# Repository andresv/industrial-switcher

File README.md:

## industrial-switcher

This board is meant for switching various 24V loads, like coils and relays.

## Requirements

[PlatformIO](http://platformio.org) is used for building.

```
pip install -U pip setuptools
pip install -U platformio
platformio platforms install timsp430
```

## Build and upload
```
platformio run
platformio run --target upload
```

## License

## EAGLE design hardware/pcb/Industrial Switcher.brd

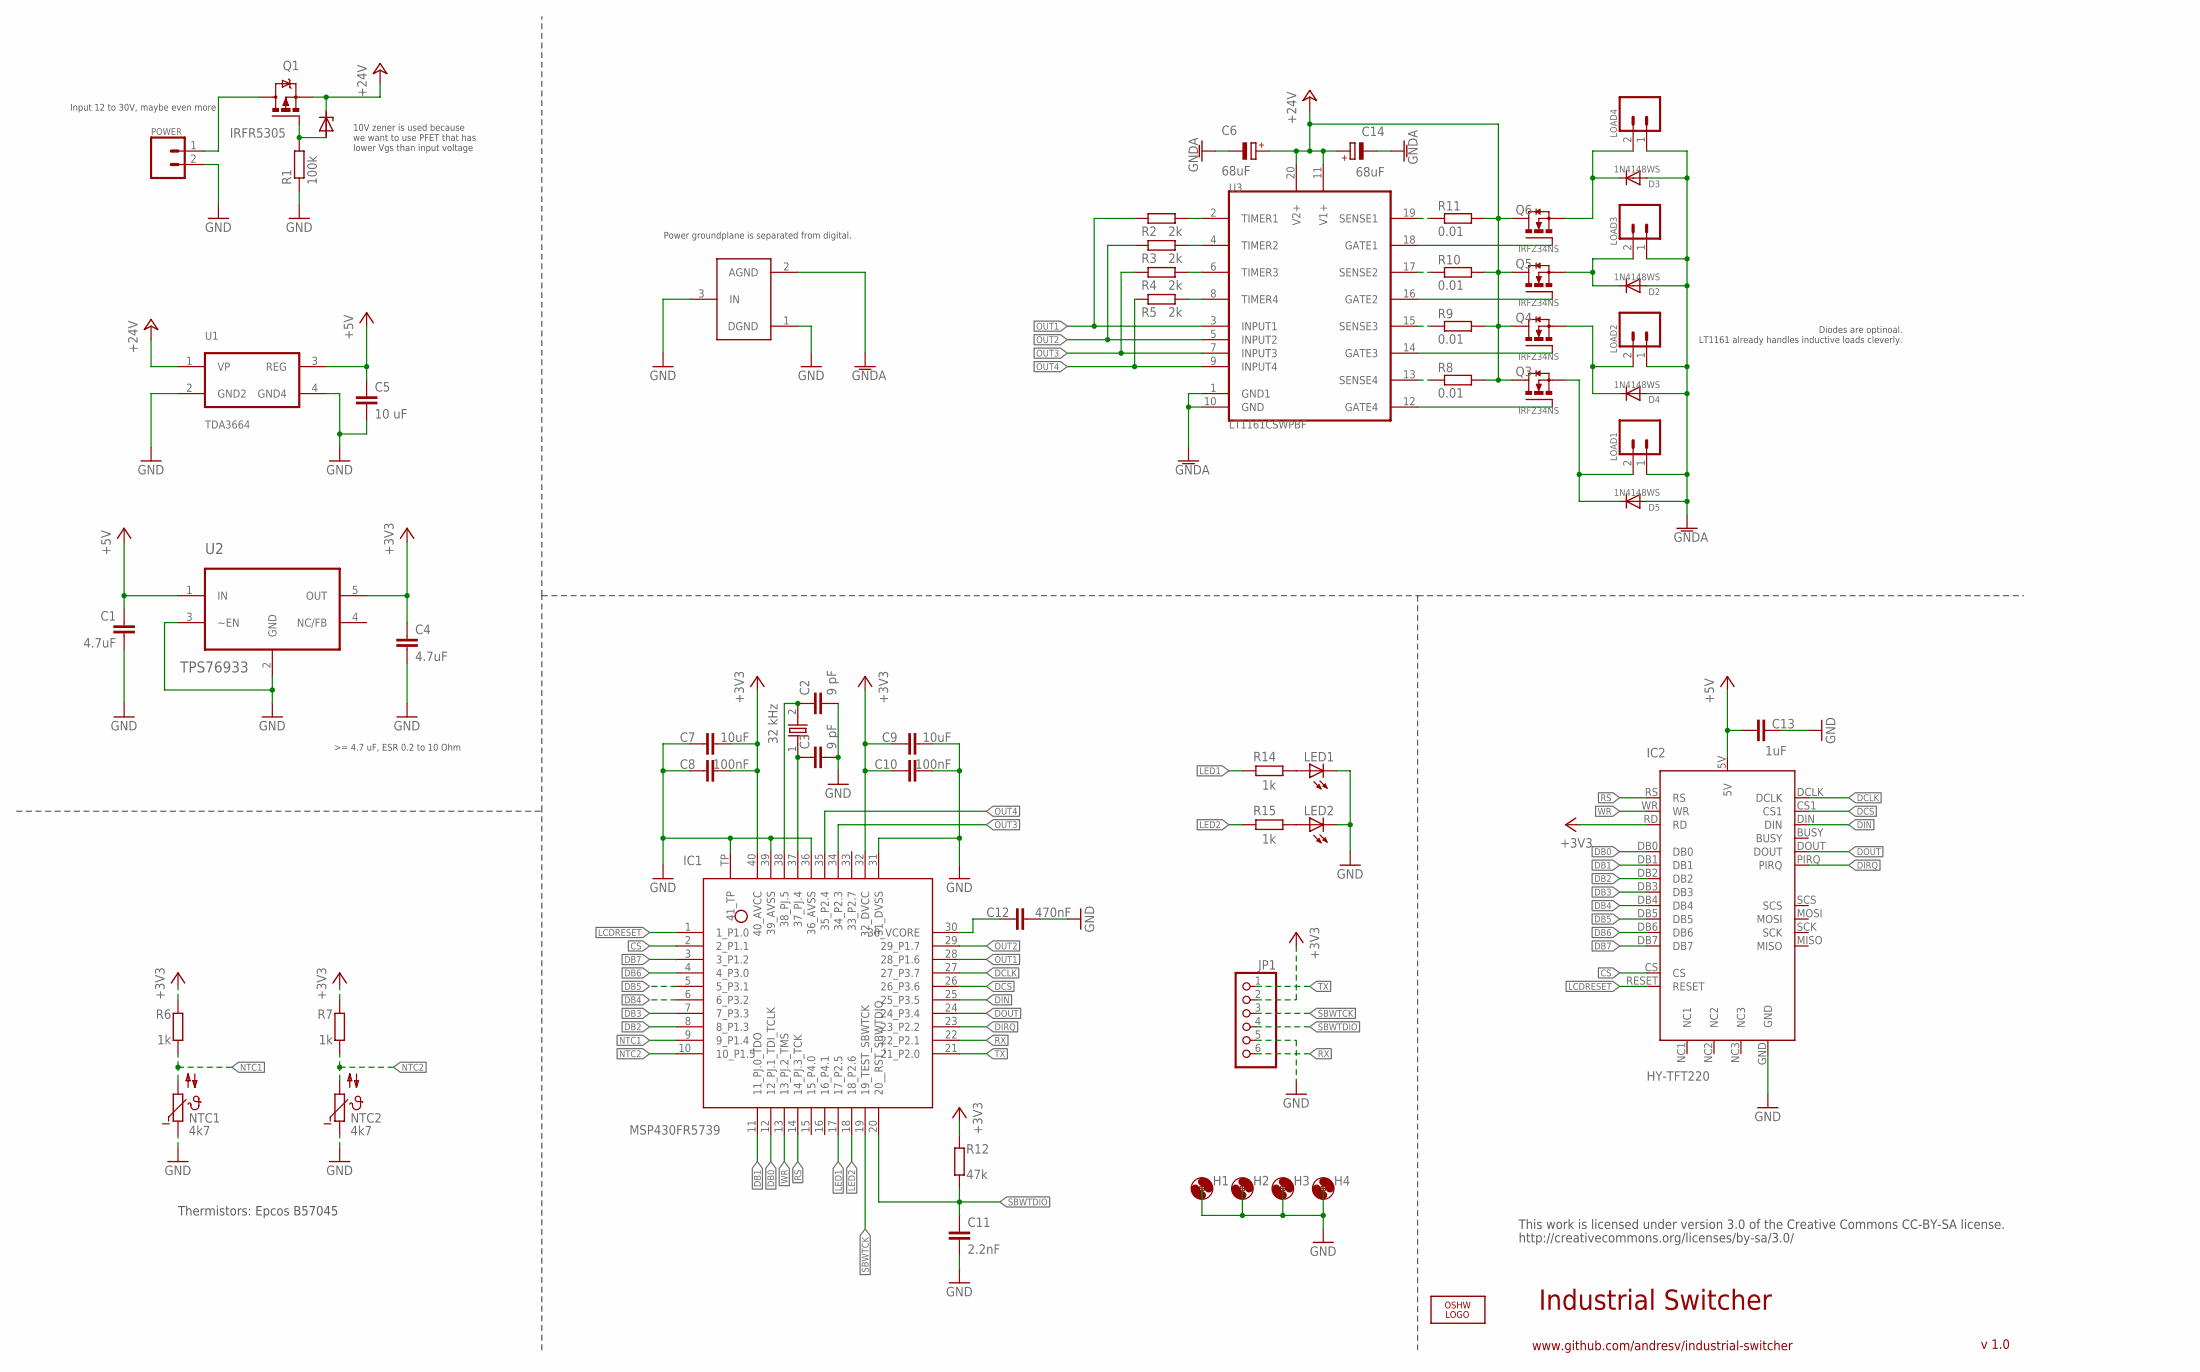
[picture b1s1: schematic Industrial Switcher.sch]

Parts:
C1: 4.7uF; C0805
C2, C3: 9 pF; C0402
C4: 4.7uF; C1206
C5: 10 uF; C1206
C6, C14: 68uF; PANASONIC_F
C7, C9: 10uF; C0603
C8, C10: 100nF; C0603
C11: 2.2nF; C0402
C12: 470nF; C0603
C13: 1uF; C0805
D1: 10V; SOD323-W
D2, D3, D4, D5: 1N4148WS; SOD323-W
H1, H2, H3, H4: MOUNT-HOLE3.0; 3,0
IC1: MSP430FR5739; RHA40
IC2: HY-TFT220; 2.2TFT
JP1: PINHD-1X6; 1X06
LED1, LED2: LEDCHIP-LED0603; CHIP-LED0603
LOAD1, LOAD2, LOAD3, LOAD4: M025MM; SCREWTERMINAL-5MM-2
LOGO1: OSHW_LOGO_8MILX0350-NT; OSHW_8X350_NOTEXT
NTC1, NTC2: 4k7; N640
POWER: M025MM; SCREWTERMINAL-5MM-2
Q1: IRFR5305; D-PAK_TO252AA
Q2: 32 kHz; ABS07
Q3, Q4, Q5, Q6: IRFZ34NS; D2PACK
R1: 100k; R0603
R2, R3, R4, R5: 2k; R0603
R6, R7: 1k; R0603
R8, R9, R10, R11: 0.01; R0603
R12: 47k; R0402
R14, R15: 1k; R0402
U1: TDA3664; DRFRIEDPARTS/DOAAZ
U2: TPS76933; SOT95P280X145-5N
U3: LT1161CSWPBF; ANDRESV/B3JU7
U$1: GND_CONNECT

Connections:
+3V3: C4.1, C7.2, C8.2, C9.1, C10.1, IC1.32 (32_DVCC), IC1.40 (40_AVCC), IC2.RD, JP1.2, R6.2, R7.2, R12.2, U2.5 (OUT)
+5V: C1.1, C5.1, C13.2, IC2.5V, U1.3 (REG), U2.1 (IN)
+24V: C6.+, C14.+, D1.C, Q1.3 (S), Q3.2 (D), Q4.2 (D), Q5.2 (D), Q6.2 (D), R8.2, R9.2, R10.2, R11.2, U1.1 (VP), U3.11 (V1+), U3.20 (V2+)
CS: IC1.2 (2_P1.1), IC2.CS
DB0: IC1.12 (12_PJ.1_TDI_TCLK), IC2.DB0
DB1: IC1.11 (11_PJ.0_TDO), IC2.DB1
DB2: IC1.8 (8_P1.3), IC2.DB2
DB3: IC1.7 (7_P3.3), IC2.DB3
DB4: IC1.6 (6_P3.2), IC2.DB4
DB5: IC1.5 (5_P3.1), IC2.DB5
DB6: IC1.4 (4_P3.0), IC2.DB6
DB7: IC1.3 (3_P1.2), IC2.DB7
DCLK: IC1.27 (27_P3.7), IC2.DCLK
DCS: IC1.26 (26_P3.6), IC2.CS1
DIN: IC1.25 (25_P3.5), IC2.DIN
DIRQ: IC1.23 (23_P2.2), IC2.PIRQ
DOUT: IC1.24 (24_P3.4), IC2.DOUT
GND: C1.2, C2.2, C3.2, C4.2, C5.2, C7.1, C8.1, C9.2, C10.2, C11.2, C12.2, C13.1, IC1.31 (31_DVSS), IC1.36 (36_AVSS), IC1.39 (39_AVSS), IC1.TP (41_TP), IC2.GND, JP1.5, LED1.C, LED2.C, NTC1.1, NTC2.1, POWER.2, R1.1, U1.2 (GND2), U1.4 (GND4), U2.2 (GND), U2.3 (~EN), U$1.1 (DGND), U$1.3 (IN)
GNDA: C6.-, C14.-, D2.A, D3.A, D4.A, D5.A, LOAD1.1, LOAD2.1, LOAD3.1, LOAD4.1, U3.1 (GND1), U3.10 (GND), U$1.2 (AGND)
LCDRESET: IC1.1 (1_P1.0), IC2.RESET
LED1: IC1.17 (17_P2.5), R14.2
LED2: IC1.18 (18_P2.6), R15.2
unnamed: D1.A, Q1.1 (G), R1.2
unnamed: R5.2, U3.8 (TIMER4)
unnamed: R8.1, U3.13 (SENSE4)
unnamed: R9.1, U3.15 (SENSE3)
unnamed: D3.C, LOAD4.2, Q6.3 (S)
unnamed: R10.1, U3.17 (SENSE2)
unnamed: R4.2, U3.6 (TIMER3)
unnamed: D2.C, LOAD3.2, Q5.3 (S)
unnamed: R11.1, U3.19 (SENSE1)
unnamed: R3.2, U3.4 (TIMER2)
unnamed: D4.C, LOAD2.2, Q4.3 (S)
unnamed: POWER.1, Q1.4 (D)
unnamed: R2.2, U3.2 (TIMER1)
unnamed: D5.C, LOAD1.2, Q3.3 (S)
unnamed: Q6.1 (G), U3.18 (GATE1)
unnamed: C3.1, IC1.37 (37_PJ.4), Q2.1
unnamed: C2.1, IC1.38 (38_PJ.5), Q2.2
unnamed: C12.1, IC1.30 (30_VCORE)
unnamed: Q5.1 (G), U3.16 (GATE2)
unnamed: Q4.1 (G), U3.14 (GATE3)
unnamed: Q3.1 (G), U3.12 (GATE4)
unnamed: LED1.A, R14.1
unnamed: LED2.A, R15.1
NTC1: IC1.9 (9_P1.4), NTC1.2, R6.1
NTC2: IC1.10 (10_P1.5), NTC2.2, R7.1
OUT1: IC1.28 (28_P1.6), R2.1, U3.3 (INPUT1)
OUT2: IC1.29 (29_P1.7), R3.1, U3.5 (INPUT2)
OUT3: IC1.34 (34_P2.3), R4.1, U3.7 (INPUT3)
OUT4: IC1.35 (35_P2.4), R5.1, U3.9 (INPUT4)
RS: IC1.14 (14_PJ.3_TCK), IC2.RS
RX: IC1.22 (22_P2.1), JP1.6
SBWTCK: IC1.19 (19_TEST_SBWTCK), JP1.3
SBWTDIO: C11.1, IC1.20 (20__RST_SBWTDIO), JP1.4, R12.1
TX: IC1.21 (21_P2.0), JP1.1
WR: IC1.13 (13_PJ.2_TMS), IC2.WR

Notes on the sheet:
Industrial Switcher
www.github.com/andresv/industrial-switcher
v 1.0
This work is licensed under version 3.0 of the Creative Commons CC-BY-SA license.
http://creativecommons.org/licenses/by-sa/3.0/
Thermistors: Epcos B57045
10V zener is used because we want to use PFET that has lower Vgs than input voltage
Diodes are optinoal. LT1161 already handles inductive loads cleverly.
Input 12 to 30V, maybe even more
Power groundplane is separated from digital.

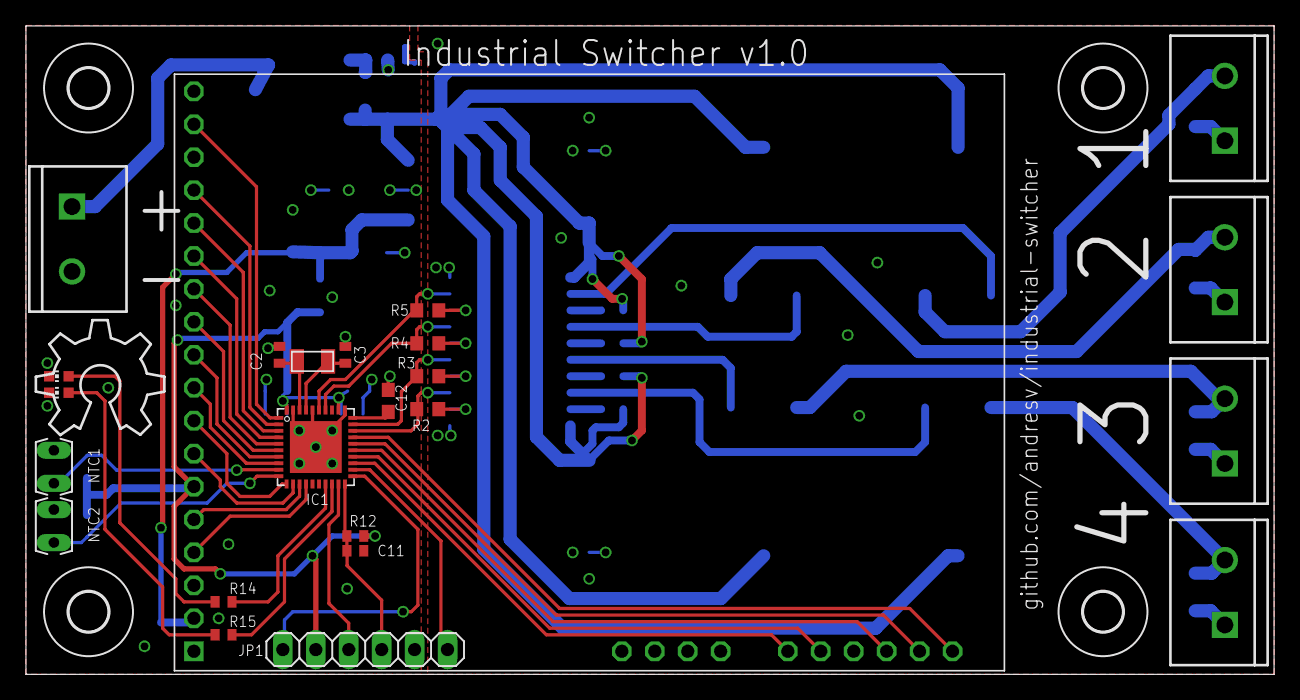
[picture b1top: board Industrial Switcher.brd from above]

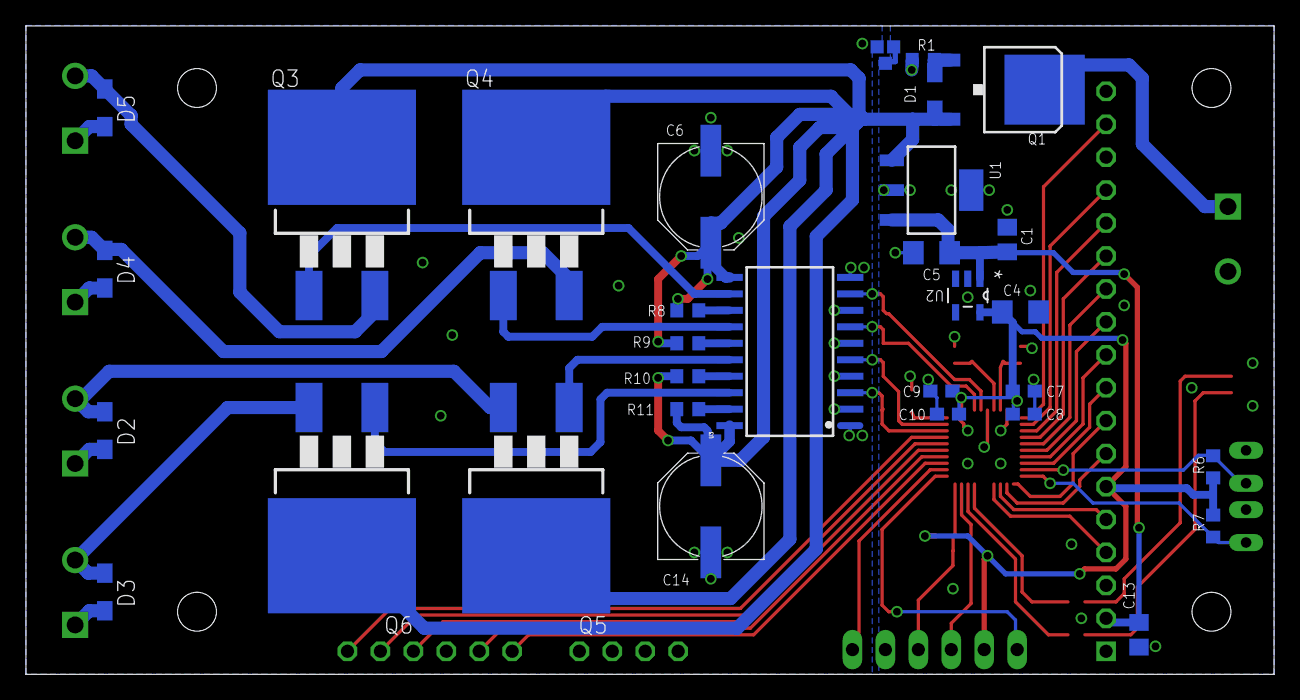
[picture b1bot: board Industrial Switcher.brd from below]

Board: 2 copper layers, 96.2 x 50.0 mm, 60 parts (31 on the bottom side), 57 nets.

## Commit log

2013-02-24 Added initial schematic
2013-02-24 Routing almost finished.
2013-02-25 Rearranged pins for better layout.
2013-02-26 Added LEDs and did some more routing.
2013-02-27 PCB seems to be now ready
2013-02-28 Added optional flyback diodes to loads.
2013-02-28 Separated digital and power groundplane.
2013-03-02 Replaced OSHW logo.
2013-03-25 added garage.c
2013-04-06 Removed garage.c
2013-04-06 Added garage.ino, Energia is going to be used.
2013-04-06 Added v2.1 UTFT library.
    Library is downloaded from: http://www.henningkarlsen.com/electronics/library.php?id=51
2013-04-07 Added Energia support to UTFT library.
    Currently only 8 bit HX8340B_8 display is tested on custom MSP430FR5739 board.
2013-04-07 Added trivial TFT use case to garage.ino
2013-04-07 Added DISABLE_CHAR_ROTATING flag to UTFT
    Character rotating takes huge amount of memory on msp430fr5739, now it is possible to disable this feature to save memory.
2013-04-08 Moved DISABLE_CHAR_ROTATING to memorysaver.h
2013-04-08 Added garage mock GUI elements
2013-04-08 Moved garage label to bottom
2013-04-09 Added UTouch 1.0 lib
2013-04-09 Added 2.2" calibration constants
2013-04-09 Added touch support.
2013-04-10 Implemented set temp chooser and added NTC table.
2013-04-10 Added on-off regulator with hysteresis.
2013-04-11 Added high temp countdown clock
2013-04-11 Fixed number padding, added status LED
2013-04-12 Added current state saving to FRAM
2013-11-29 add temperature input smoothing and discard strange values
2013-12-24 add better temperature filtering and outliers discarding
2013-12-24 add vishay 5k NTC table
2013-12-24 remove duplications from switch functions
2013-12-25 decrease hysteresis and smoothing buffer size
2015-12-19 migrate to platformio build system
2015-12-28 try to set F_CPU to 8 MHz and turn on red LED on boot

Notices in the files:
parts and their libraries:
SparkFun-Passives: Licensing: CC v3.0 Share-Alike You are welcome to use this library for commercial purposes.
